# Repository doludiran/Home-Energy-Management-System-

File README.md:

# Home-Energy-Management-System-
This system retrieves dynamic electricity pricing information from a utility portal and automatically schedules  large residential loads like EV charging to reduce the overall cost of energy consumed 

The design involves and consists of:
• A Central Control Unit using a Linux based Raspberry Pi programmed in Python. Components of this unit included a touch screen graphic
user interface, secure Internet interface for the automatic retrieval of dynamic pricing information from a utility web portal and xbee wireless
communication interface (zigbee) for remote switching as well as load telemetry data transmission
• A Device Energy Monitoring Unit using an ARM Cortex-M3 based Microcontroller. Components of this unit included a xbee wireless interface
(zigbee) for transmitting monitoring data as well as receiving switching commands from the Central Control Unit, Analog Circuitry for AC load
switching and power consumption measurement (AC Voltage and Current)
• An optimization algorithm to minimize power cost using SciPY
• Multi-threaded programming in c and Python
• Printed Circuit Boards (PCB) design including soldering of Surface-Mount ICs (SMT)
• Hardware and printed circuit board testing and validation
• Component selection and assembly designed to comply with CSA standards

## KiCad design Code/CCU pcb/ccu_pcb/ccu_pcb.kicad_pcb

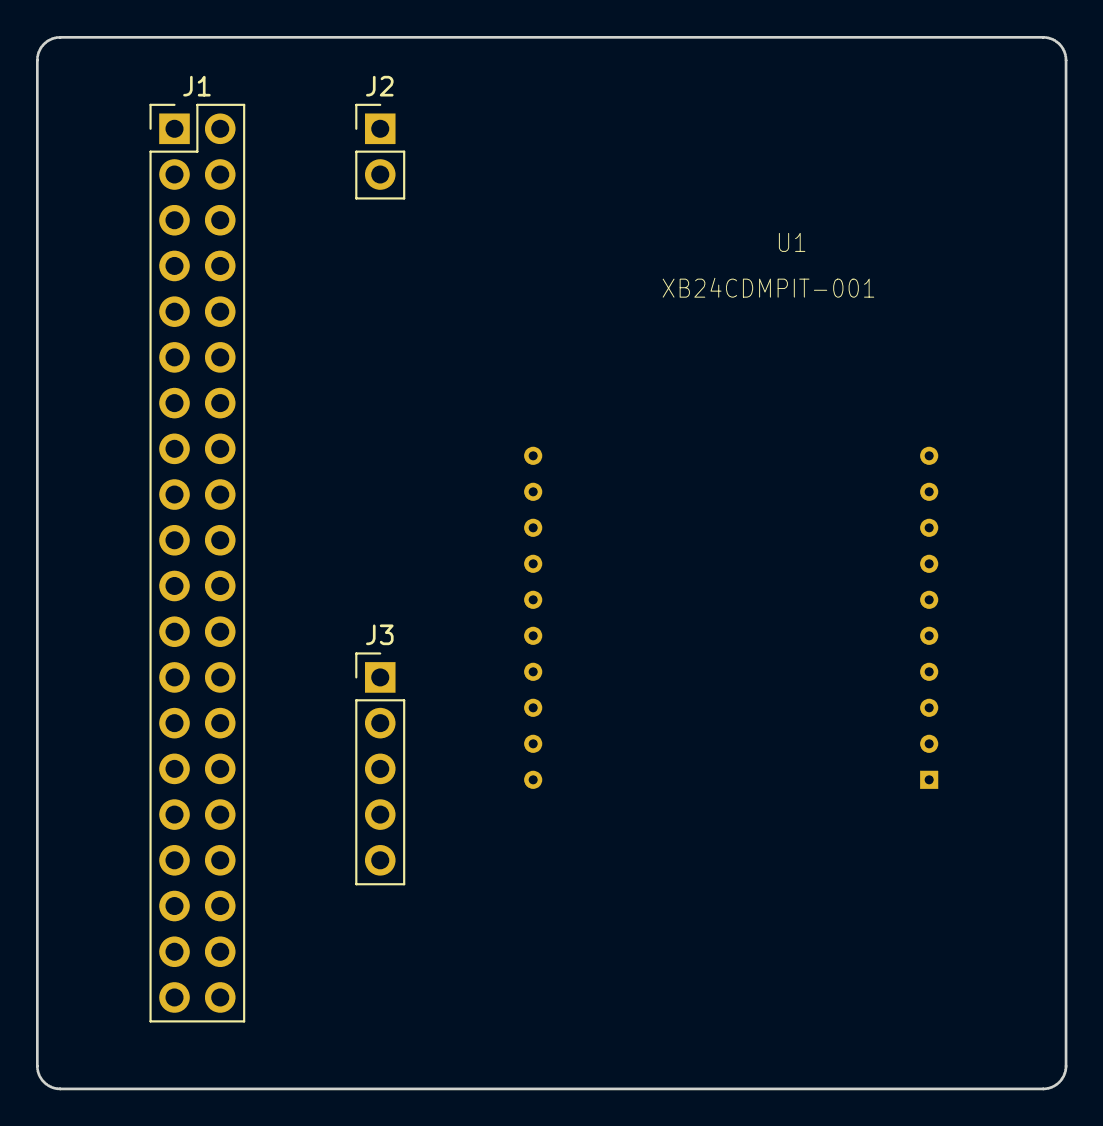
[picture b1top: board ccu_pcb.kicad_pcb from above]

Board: 2 copper layers, 57.2 x 58.4 mm, 4 parts (0 on the bottom side), 8 nets, no tracks yet.

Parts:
J1: Conn_02x20_Odd_Even; PinHeader_2x20_P2.54mm_Vertical
J2: Conn_01x02_Male; PinHeader_1x02_P2.54mm_Vertical
J3: Conn_01x05_Male; PinHeader_1x05_P2.54mm_Vertical
U1: XB24CDMPIT-001; DIP-20

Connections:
5Vsupply: J1.2, J2.1, J3.1
GND: J1.40, J2.2, J3.5, U1.10
Therm_in_c: J1.18, J3.4
Therm_in_h: J1.16, J3.3
Therm_out: J1.12, J3.2
VCC: J1.1, U1.1
X_DIN: J1.8, U1.3
X_DOUT: J1.10, U1.2

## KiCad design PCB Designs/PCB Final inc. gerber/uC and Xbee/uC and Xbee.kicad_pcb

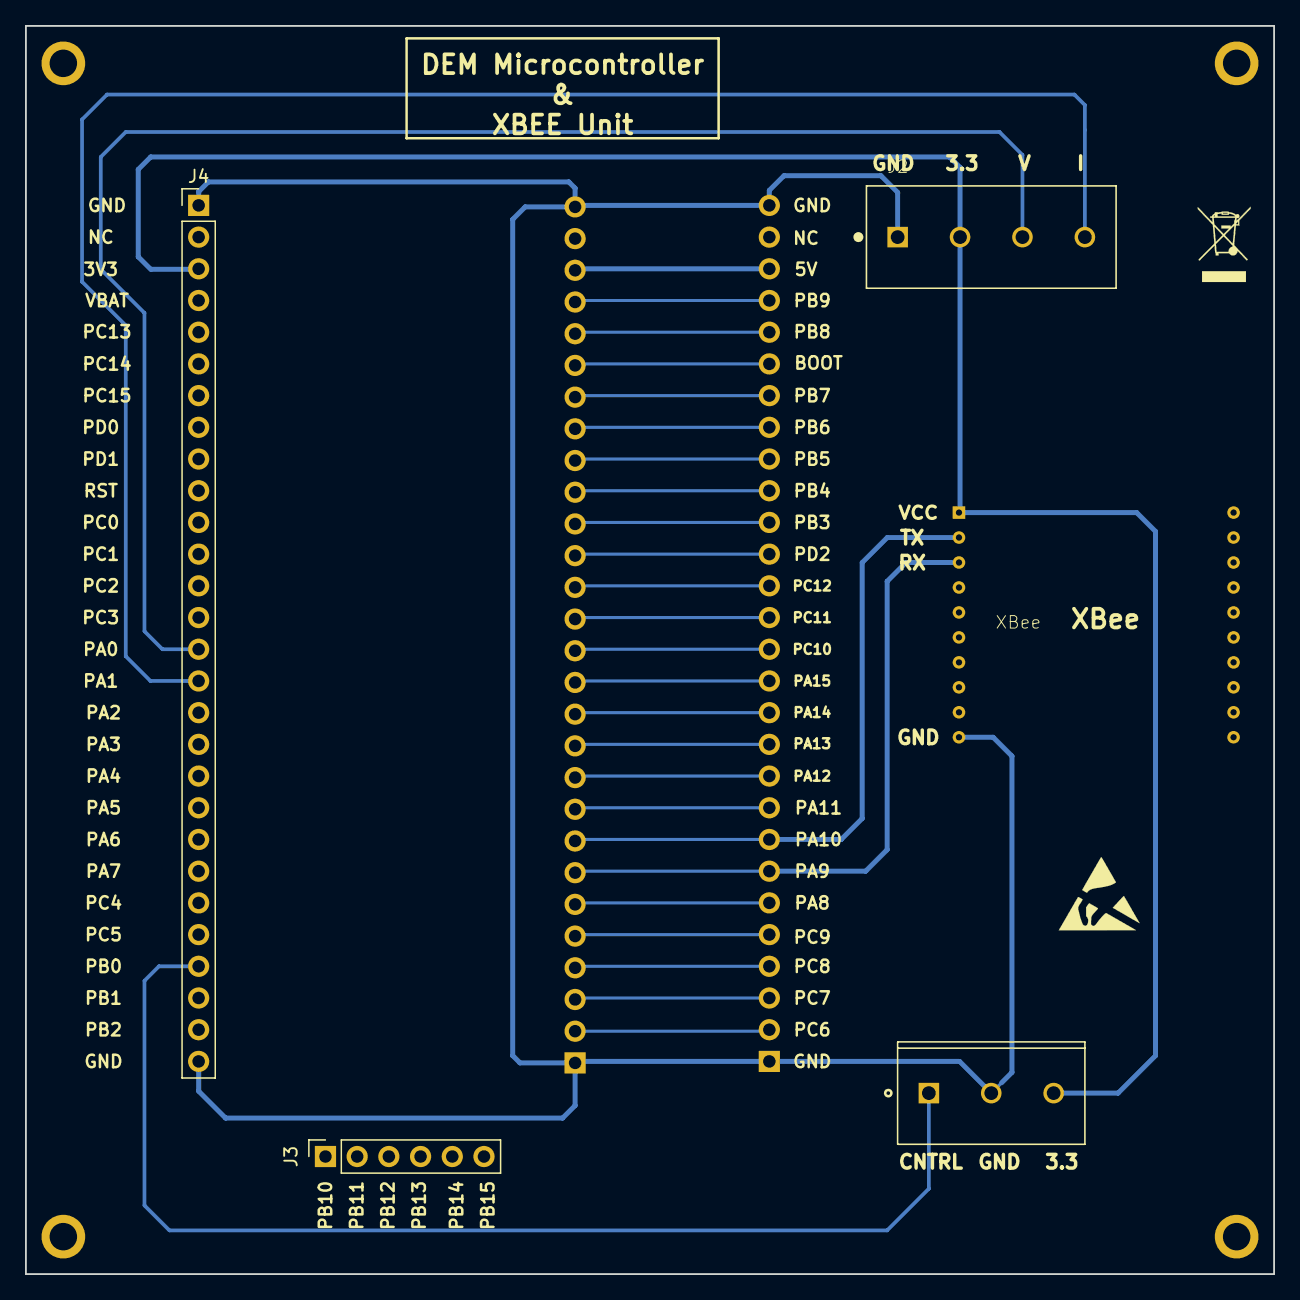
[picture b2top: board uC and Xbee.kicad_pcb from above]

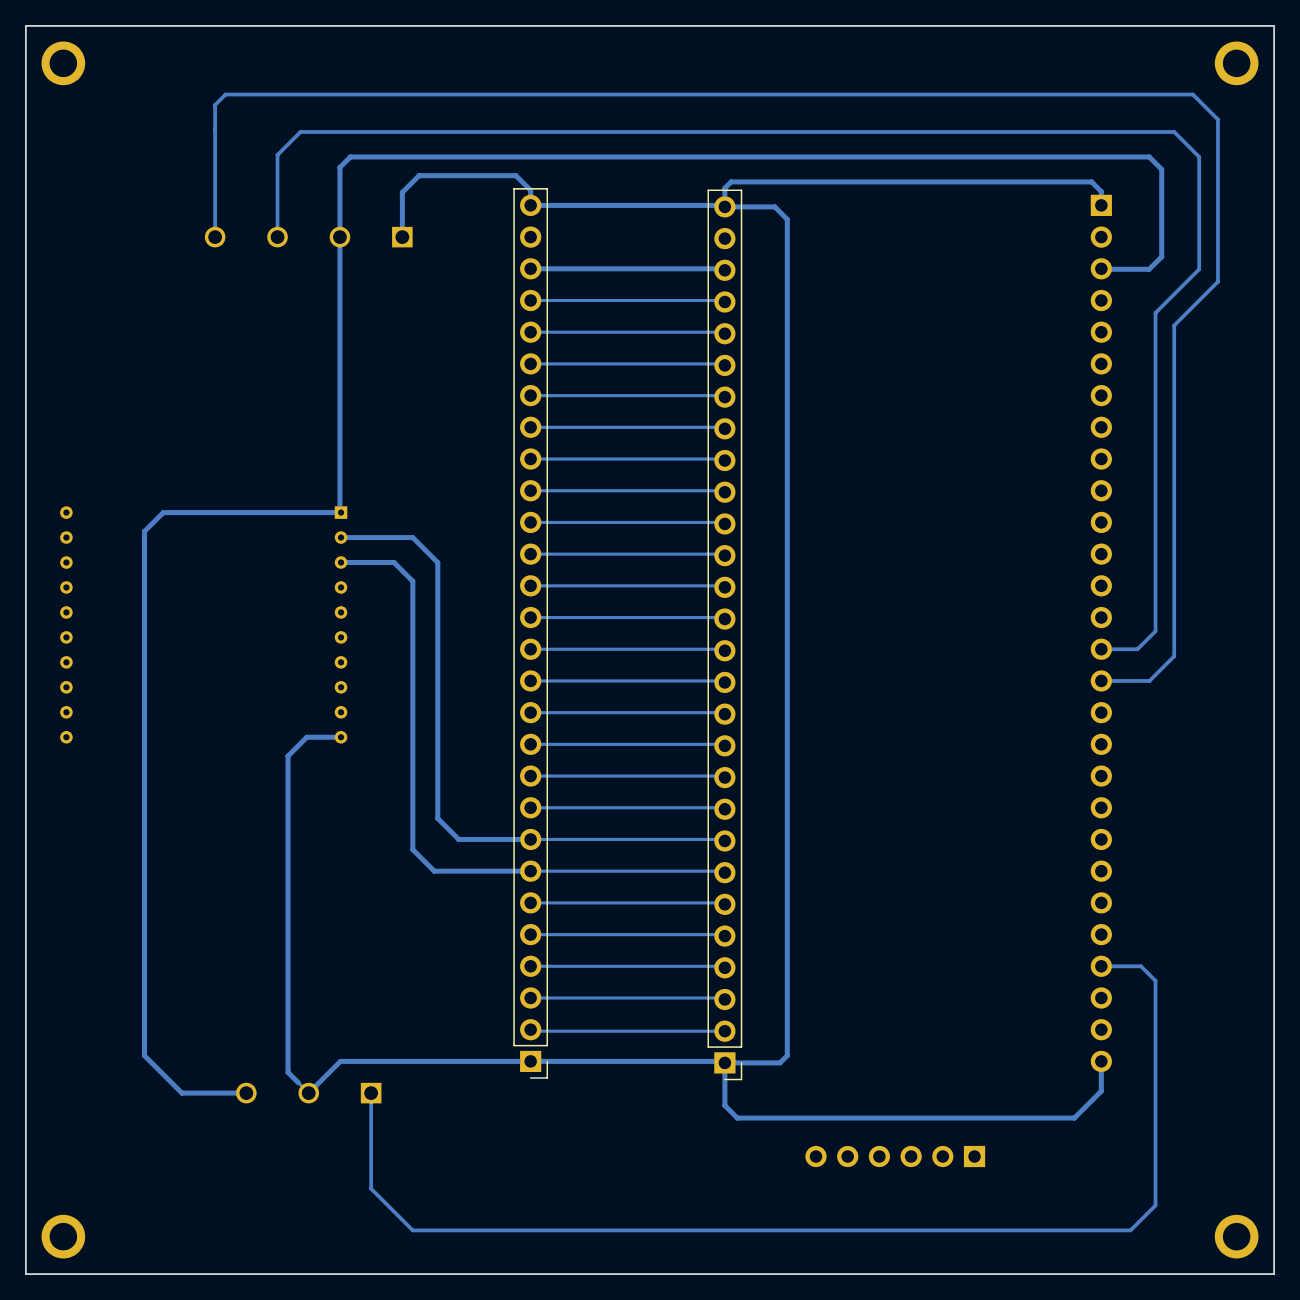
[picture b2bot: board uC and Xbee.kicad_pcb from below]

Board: 2 copper layers, 100.0 x 100.0 mm, 7 parts (2 on the bottom side), 30 nets.

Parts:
J1: 282836-3; TE_282836-3
J2: 282836-4; TE_282836-4
J3: Conn_01x06_Female; PinSocket_1x06_P2.54mm_Vertical
J4, J5, J6: Conn_01x28_Female; PinHeader_1x28_P2.54mm_Vertical
U1: XB24CDMSIT-001; DIP-20

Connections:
3.3V1: J1.3, J2.2, J4.3, U1.1
5V: J5.26, J6.26
BOOT: J5.23, J6.23
GND1: J1.2, J2.1, J4.1, J4.28, J5.1, J5.28, J6.1, J6.28, U1.10
PA0: J2.3, J4.15
PA1: J2.4, J4.16
PA8: J5.6, J6.6
PA9: J5.7, J6.7, U1.3
PA10: J5.8, J6.8, U1.2
PA11: J5.9, J6.9
PA12: J5.10, J6.10
PA13: J5.11, J6.11
PA14: J5.12, J6.12
PA15: J5.13, J6.13
PB0: J1.1, J4.25
PB3: J5.18, J6.18
PB4: J5.19, J6.19
PB5: J5.20, J6.20
PB6: J5.21, J6.21
PB7: J5.22, J6.22
PB8: J5.24, J6.24
PB9: J5.25, J6.25
PC6: J5.2, J6.2
PC7: J5.3, J6.3
PC8: J5.4, J6.4
PC9: J5.5, J6.5
PC10: J5.14, J6.14
PC11: J5.15, J6.15
PC12: J5.16, J6.16
PD2: J5.17, J6.17

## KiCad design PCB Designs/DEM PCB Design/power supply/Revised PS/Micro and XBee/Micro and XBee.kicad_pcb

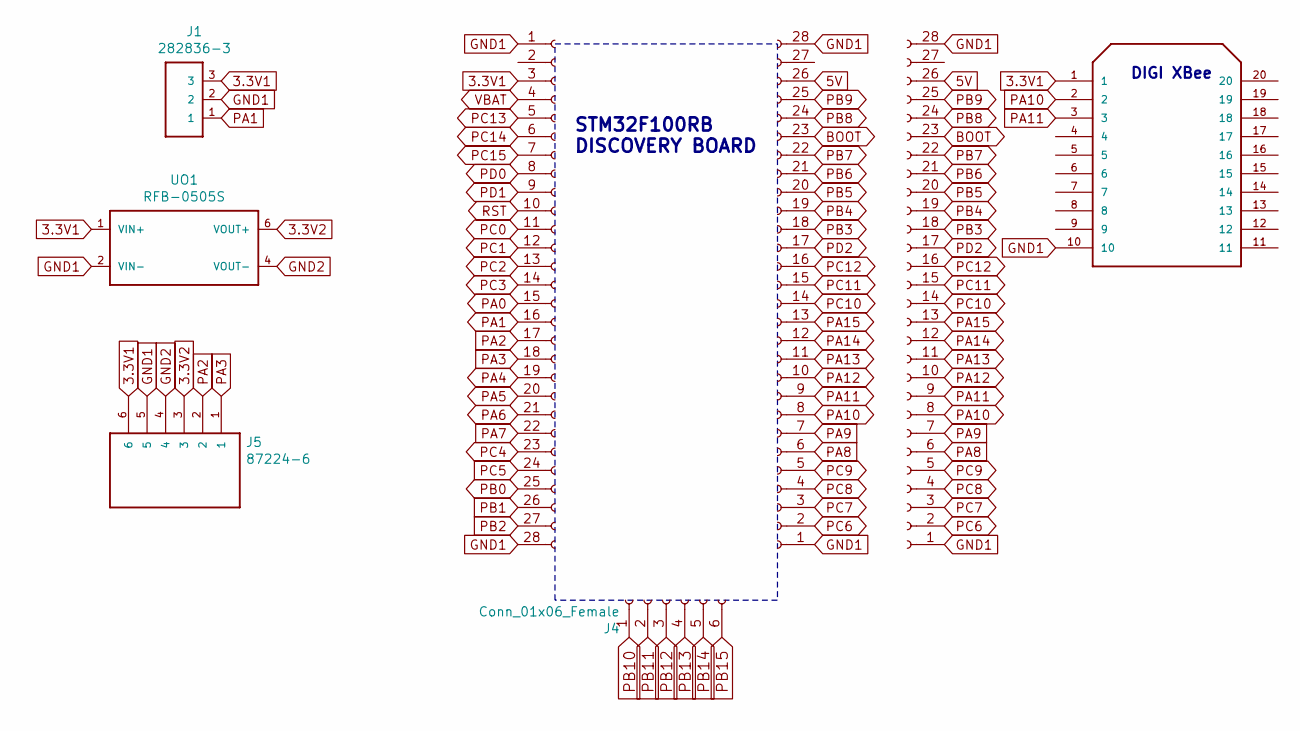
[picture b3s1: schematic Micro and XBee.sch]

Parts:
J1: 282836-3; TE_282836-3
J2, J3, J6: Conn_01x28_Female; PinHeader_1x28_P2.54mm_Vertical
J4: Conn_01x06_Female; PinSocket_1x06_P2.54mm_Vertical
J5: 87224-6; TE_87224-6
U2: XB24CDMSIT-001; DIP-20
UO1: RFB-0505S

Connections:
3.3V1: J1.3, J2.3, J5.6, U2.1, UO1.1 (VIN+)
3.3V2: J5.3, UO1.6 (VOUT+)
5V: J3.26, J6.26
BOOT: J3.23, J6.23
GND1: J1.2, J2.1, J2.28, J3.1, J3.28, J5.5, J6.1, J6.28, U2.10, UO1.2 (VIN-)
GND2: J5.4, UO1.4 (VOUT-)
PA0: J2.15
PA1: J1.1, J2.16
PA2: J2.17, J5.2
PA3: J2.18, J5.1
PA4: J2.19
PA5: J2.20
PA6: J2.21
PA7: J2.22
PA8: J3.6, J6.6
PA9: J3.7, J6.7
PA10: J3.8, J6.8, U2.2
PA11: J3.9, J6.9, U2.3
PA12: J3.10, J6.10
PA13: J3.11, J6.11
PA14: J3.12, J6.12
PA15: J3.13, J6.13
PB0: J2.25
PB1: J2.26
PB2: J2.27
PB3: J3.18, J6.18
PB4: J3.19, J6.19
PB5: J3.20, J6.20
PB6: J3.21, J6.21
PB7: J3.22, J6.22
PB8: J3.24, J6.24
PB9: J3.25, J6.25
PB10: J4.1
PB11: J4.2
PB12: J4.3
PB13: J4.4
PB14: J4.5
PB15: J4.6
PC0: J2.11
PC1: J2.12
PC2: J2.13
PC3: J2.14
PC4: J2.23
PC5: J2.24
PC6: J3.2, J6.2
PC7: J3.3, J6.3
PC8: J3.4, J6.4
PC9: J3.5, J6.5
PC10: J3.14, J6.14
PC11: J3.15, J6.15
PC12: J3.16, J6.16
PC13: J2.5
PC14: J2.6
PC15: J2.7
PD0: J2.8
PD1: J2.9
PD2: J3.17, J6.17
RST: J2.10
VBAT: J2.4

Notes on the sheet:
STM32F100RB DISCOVERY BOARD
DIGI XBee

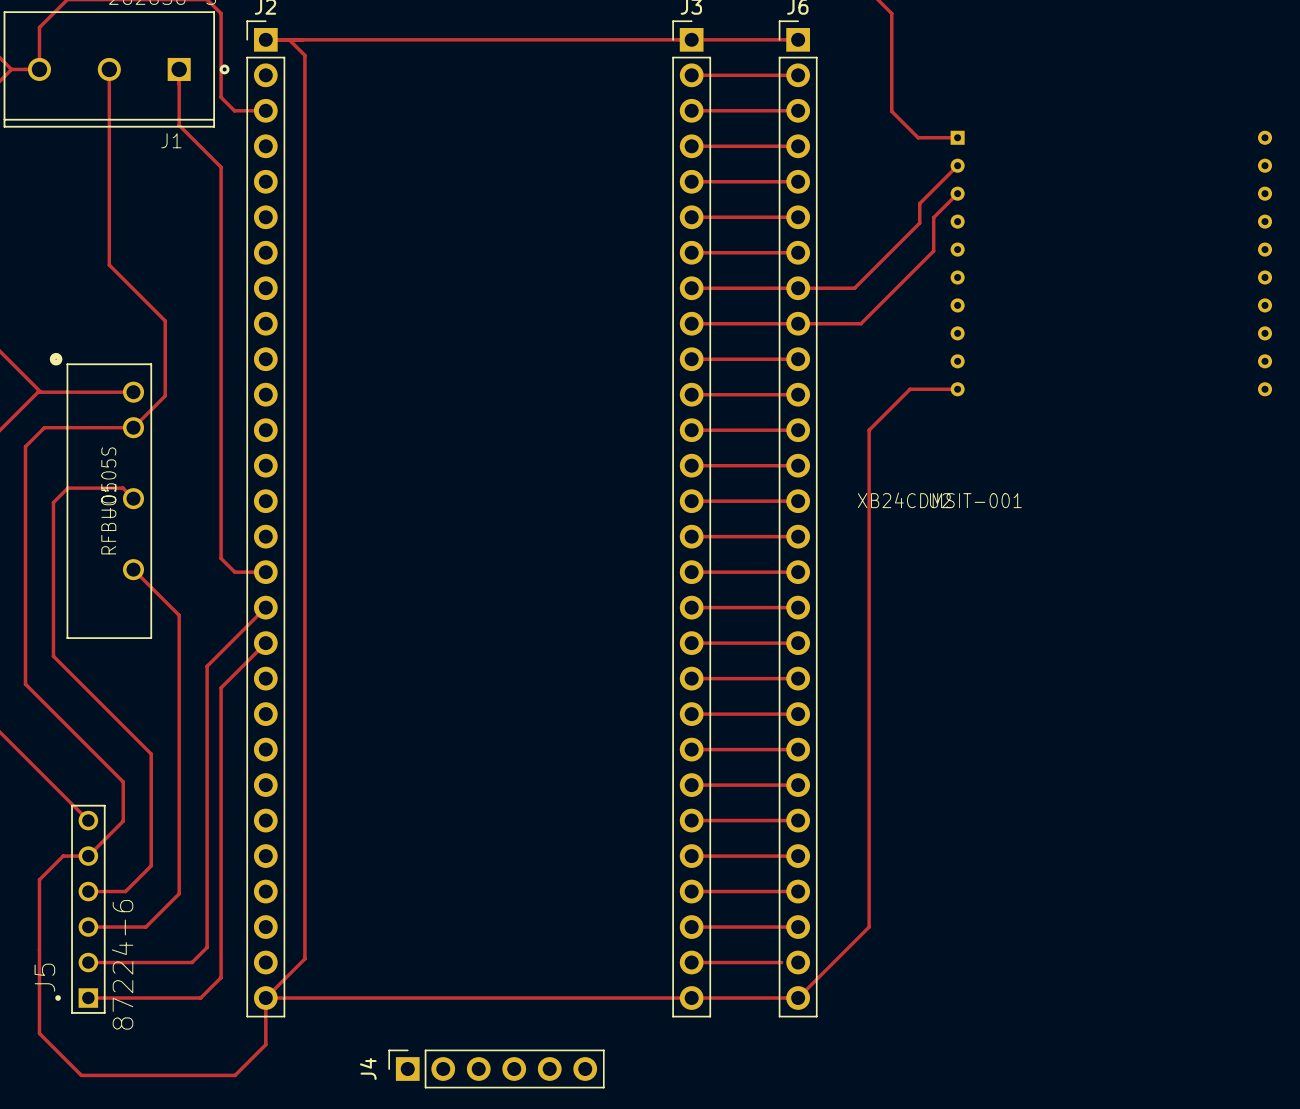
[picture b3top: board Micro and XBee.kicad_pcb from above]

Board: 2 copper layers, 8 parts (0 on the bottom side), 32 nets.

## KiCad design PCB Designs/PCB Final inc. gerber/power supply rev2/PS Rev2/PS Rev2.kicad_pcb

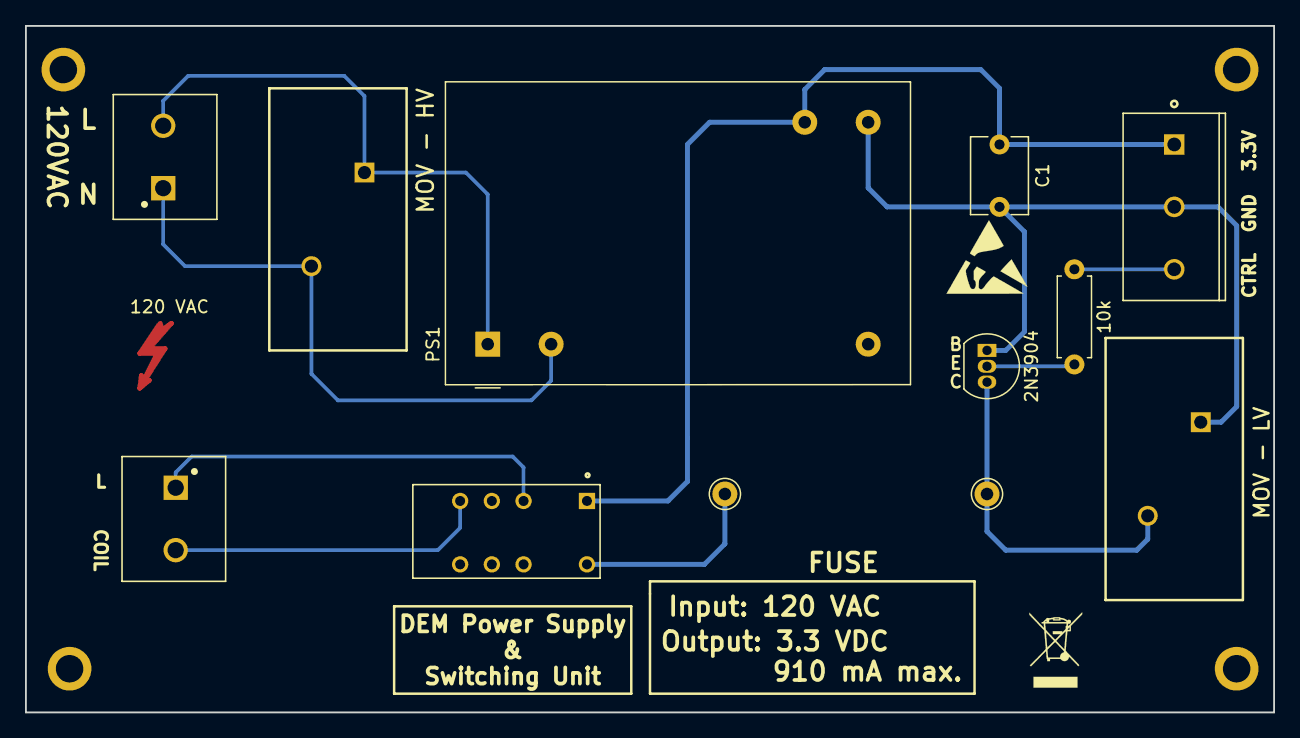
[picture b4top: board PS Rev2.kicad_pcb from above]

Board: 2 copper layers, 100.0 x 55.0 mm, 13 parts (0 on the bottom side), 10 nets.

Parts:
2N3904: 2N3904; TO-92_Inline
10k: 10k; R_Axial_DIN0207_L6.3mm_D2.5mm_P7.62mm_Horizontal
120 VAC : Symbol_Highvoltage_Type1_CopperTop_Small
C1: 400 nF; C_Disc_D6.0mm_W4.4mm_P5.00mm
J1, J3: 1935161; PHOENIX_1935161
J2: 282836-3; TE_282836-3
J4, J5: Conn_01x01_Female; Pin_D1.0mm_L10.0mm
K1: EC2-3NU; KEMET_EC2-3NU
MOV - HV: TMOV20RP300E; CAPRR750W81L2100T1100H2300P
MOV - LV: TMOV20RP300E; CAPRR750W81L2100T1100H2300P
PS1: RAC03-3.3SGA; Converter_ACDC_RECOM_RAC04-xxSGx_THT

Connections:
unnamed: C1.1, J2.1, K1.1, PS1.5
unnamed: 2N3904.1, C1.2, J2.2, MOV - LV.1, PS1.4
unnamed: J1.1, MOV - HV.2, PS1.2
unnamed: J1.2, MOV - HV.1, PS1.1
unnamed: 10k.1, J2.3
unnamed: J3.1, K1.3
unnamed: J3.2, K1.5
unnamed: 2N3904.3, J4.1, MOV - LV.2
unnamed: J5.1, K1.12
unnamed: 2N3904.2, 10k.2

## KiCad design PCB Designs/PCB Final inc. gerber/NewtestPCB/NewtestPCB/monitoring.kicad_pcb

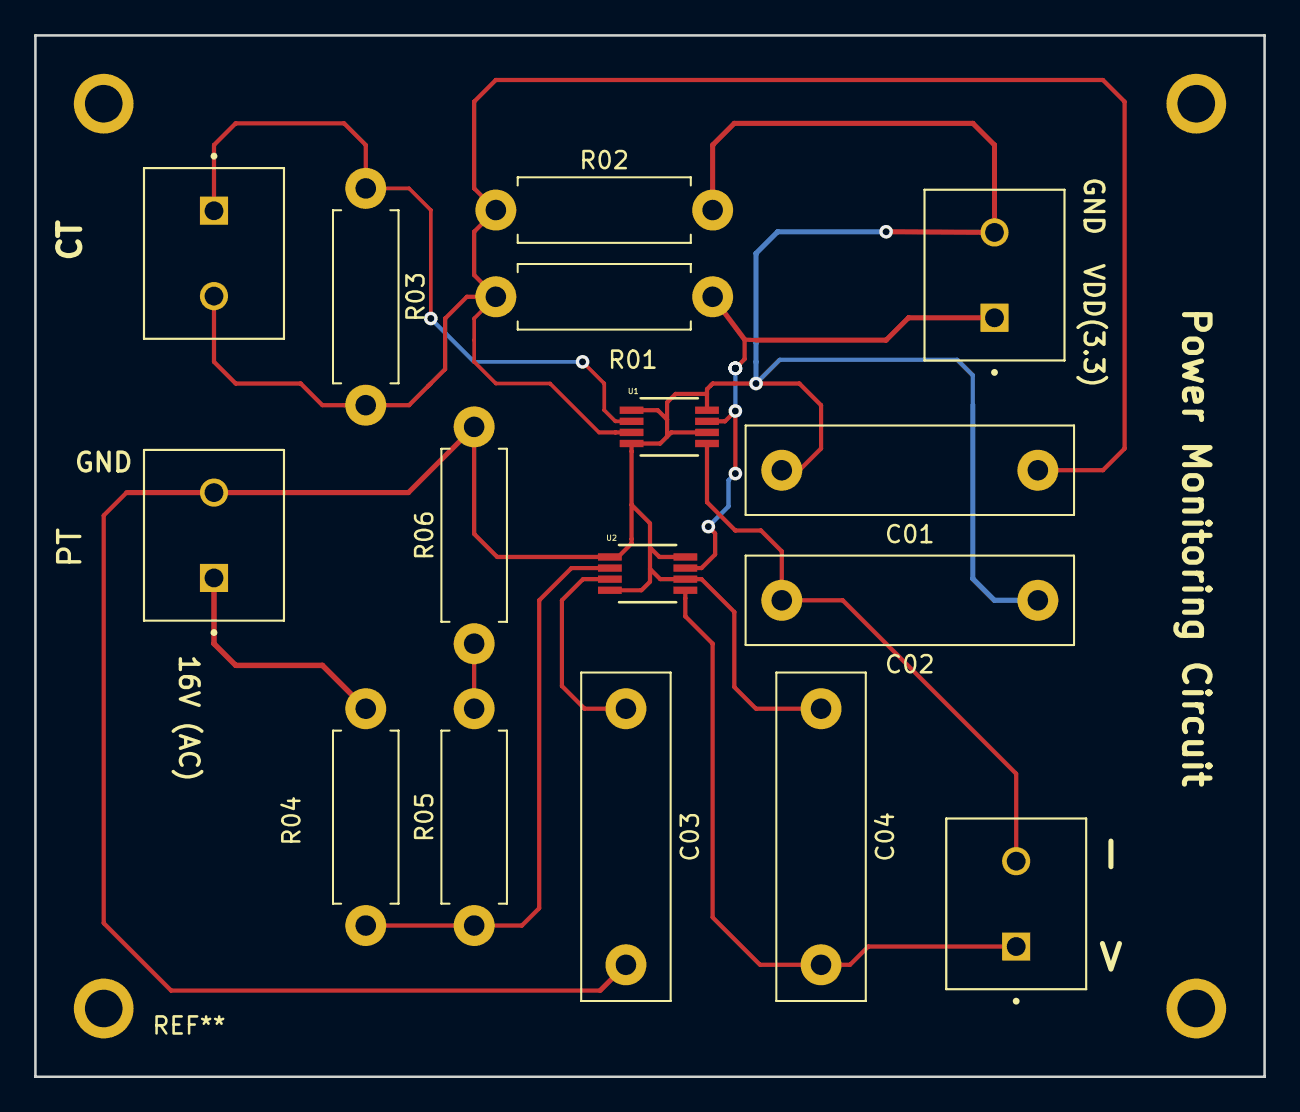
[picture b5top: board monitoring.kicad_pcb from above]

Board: 2 copper layers, 72.0 x 61.0 mm, 16 parts (0 on the bottom side), 10 nets.

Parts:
C01, C03: 0.1uF; C_Rect_L19.0mm_W5.0mm_P15.00mm_MKS4
C02, C04: 1uF; C_Rect_L19.0mm_W5.0mm_P15.00mm_MKS4
CT: 282836-2; CONN_282836-2
J3, J4: 282836-2; CONN_282836-2
PT: 282836-2; CONN_282836-2
R01, R02: 100k; R_Axial_DIN0411_L9.9mm_D3.6mm_P12.70mm_Horizontal
R03: 4; R_Axial_DIN0411_L9.9mm_D3.6mm_P12.70mm_Horizontal
R04: 10k; R_Axial_DIN0411_L9.9mm_D3.6mm_P12.70mm_Horizontal
R05: 215k; R_Axial_DIN0411_L9.9mm_D3.6mm_P12.70mm_Horizontal
R06: 1k; R_Axial_DIN0411_L9.9mm_D3.6mm_P12.70mm_Horizontal
U1, U2: LTC1966CMS8PBF; MSOP-8_MS

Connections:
unnamed: C01.1, CT.2, R01.2, R02.1, R03.2, U1.3
unnamed: C01.2, C02.1, C03.2, C04.1, J3.2, PT.2, R02.2, R06.2, U1.1, U1.4, U1.6, U1.8, U2.1, U2.4, U2.6, U2.8
unnamed: C02.2, J4.2, U1.5
unnamed: C03.1, U2.3
unnamed: C04.2, J4.1, U2.5
unnamed: CT.1, R03.1, U1.2
unnamed: PT.1, R04.1
unnamed: J3.1, R01.1, U1.7, U2.7
unnamed: R04.2, R05.1, U2.2
unnamed: R05.2, R06.1

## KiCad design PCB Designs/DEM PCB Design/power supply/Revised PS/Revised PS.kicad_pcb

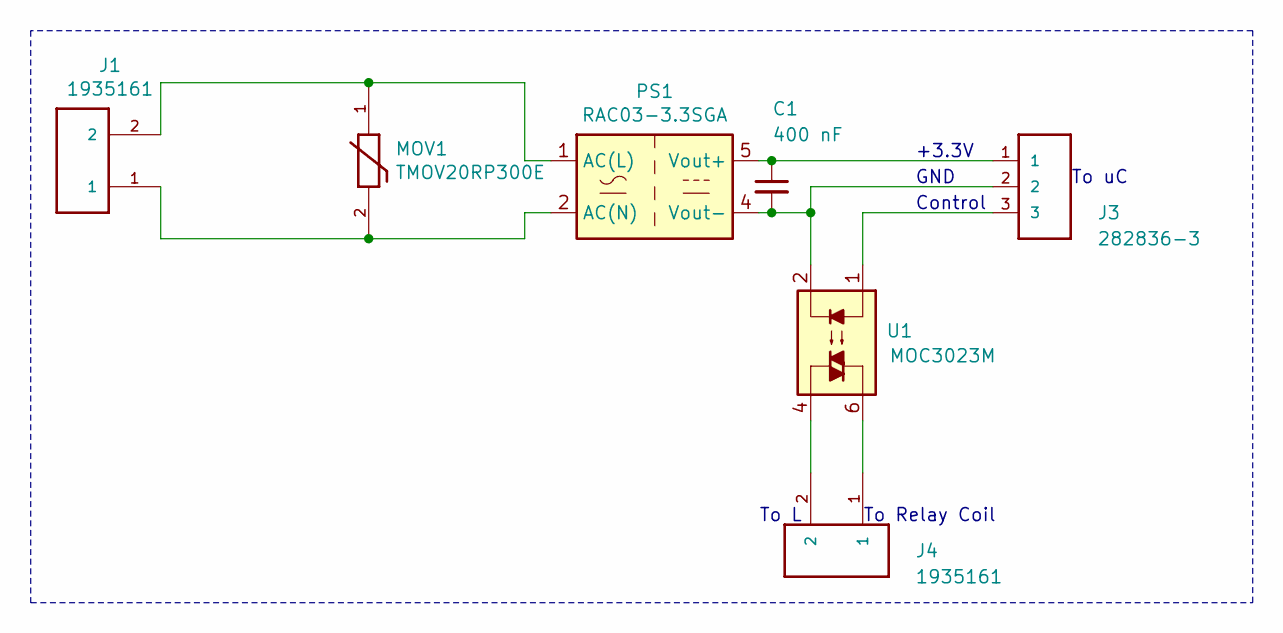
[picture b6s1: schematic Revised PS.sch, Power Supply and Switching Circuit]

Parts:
C1: 400 nF; C_Disc_D6.0mm_W4.4mm_P5.00mm
J1, J4: 1935161; PHOENIX_1935161
J3: 282836-3; TE_282836-3
MOV1: TMOV20RP300E; CAPRR750W81L2100T1100H2300P
PS1: RAC03-3.3SGA; Converter_ACDC_RECOM_RAC04-xxSGx_THT
U1: MOC3023M; DIP762W48P254L889H508Q6

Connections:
unnamed: C1.1, J3.1, PS1.5 (Vout+)
unnamed: C1.2, J3.2, PS1.4 (Vout-), U1.2
unnamed: J1.1, MOV1.2, PS1.2 (AC(N))
unnamed: J1.2, MOV1.1, PS1.1 (AC(L))
unnamed: J3.3, U1.1
unnamed: J4.1, U1.6
unnamed: J4.2, U1.4

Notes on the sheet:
To Relay Coil
To L
+3.3V
GND
Control
To uC

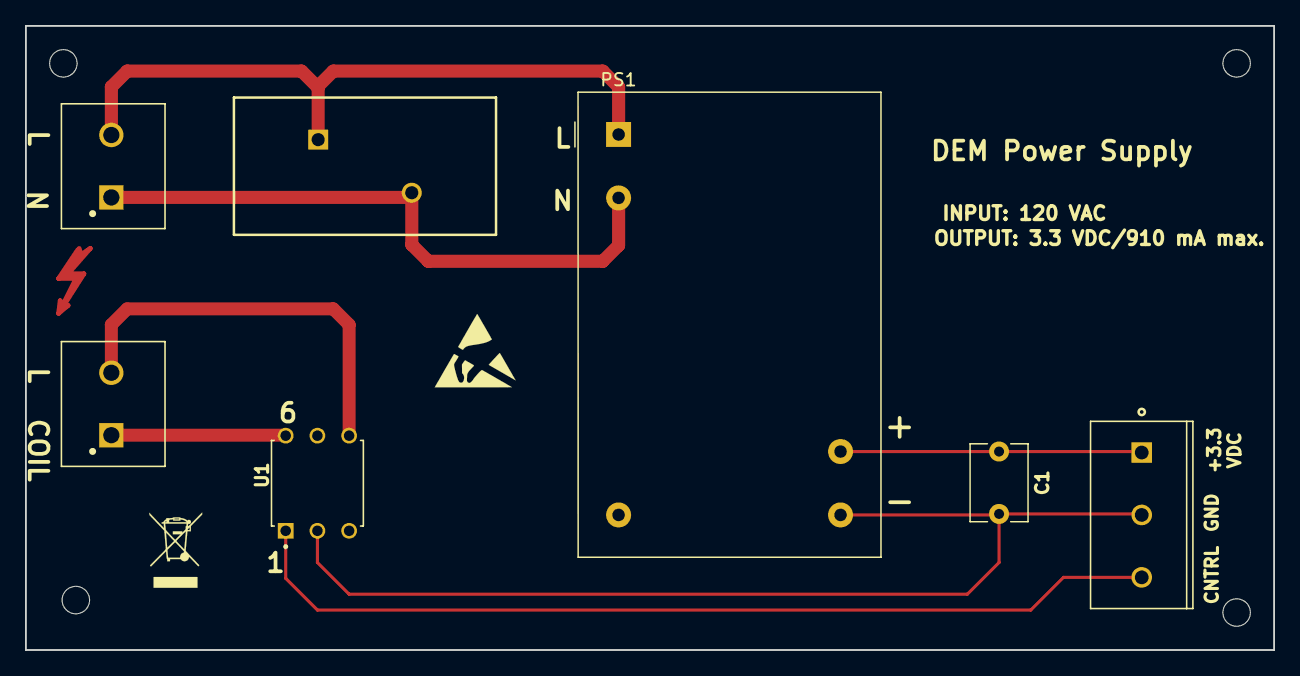
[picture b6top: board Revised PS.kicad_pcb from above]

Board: 2 copper layers, 100.0 x 50.0 mm, 7 parts (0 on the bottom side), 7 nets.

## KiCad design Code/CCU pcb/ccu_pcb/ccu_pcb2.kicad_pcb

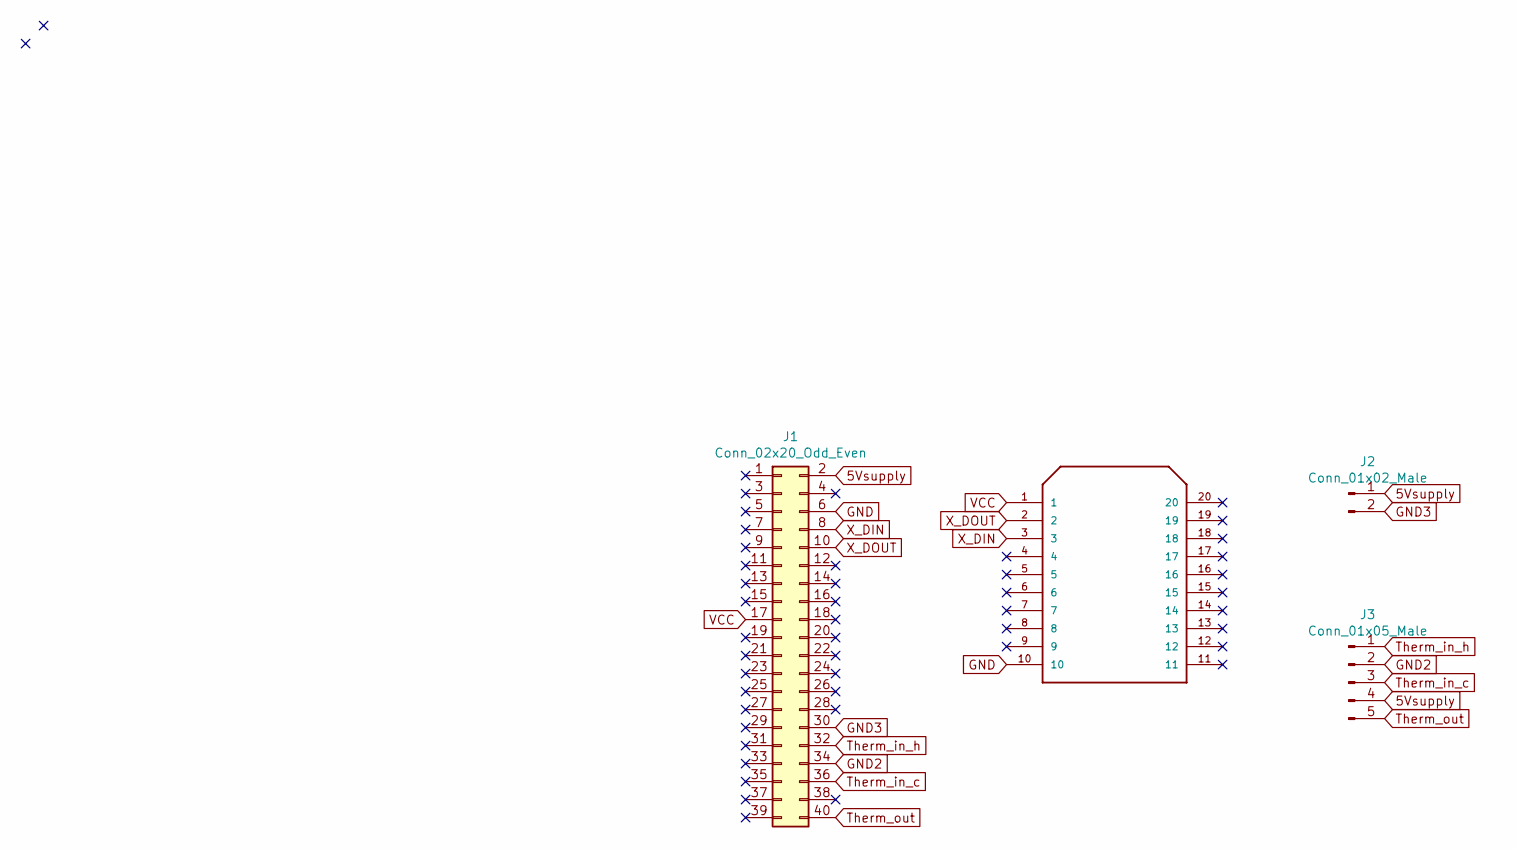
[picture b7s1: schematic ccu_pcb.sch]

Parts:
J1: Conn_02x20_Odd_Even; PinHeader_2x20_P2.54mm_Vertical
J2: Conn_01x02_Male; PinHeader_1x02_P2.54mm_Vertical
J3: Conn_01x05_Male; PinHeader_1x05_P2.54mm_Vertical
U1: XB24CDMPIT-001; DIP-20

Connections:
5Vsupply: J1.2, J2.1, J3.4
GND: J1.6, U1.10
GND2: J1.34, J3.2
GND3: J1.30, J2.2
Therm_in_c: J1.36, J3.3
Therm_in_h: J1.32, J3.1
Therm_out: J1.40, J3.5
VCC: J1.17, U1.1
X_DIN: J1.8, U1.3
X_DOUT: J1.10, U1.2

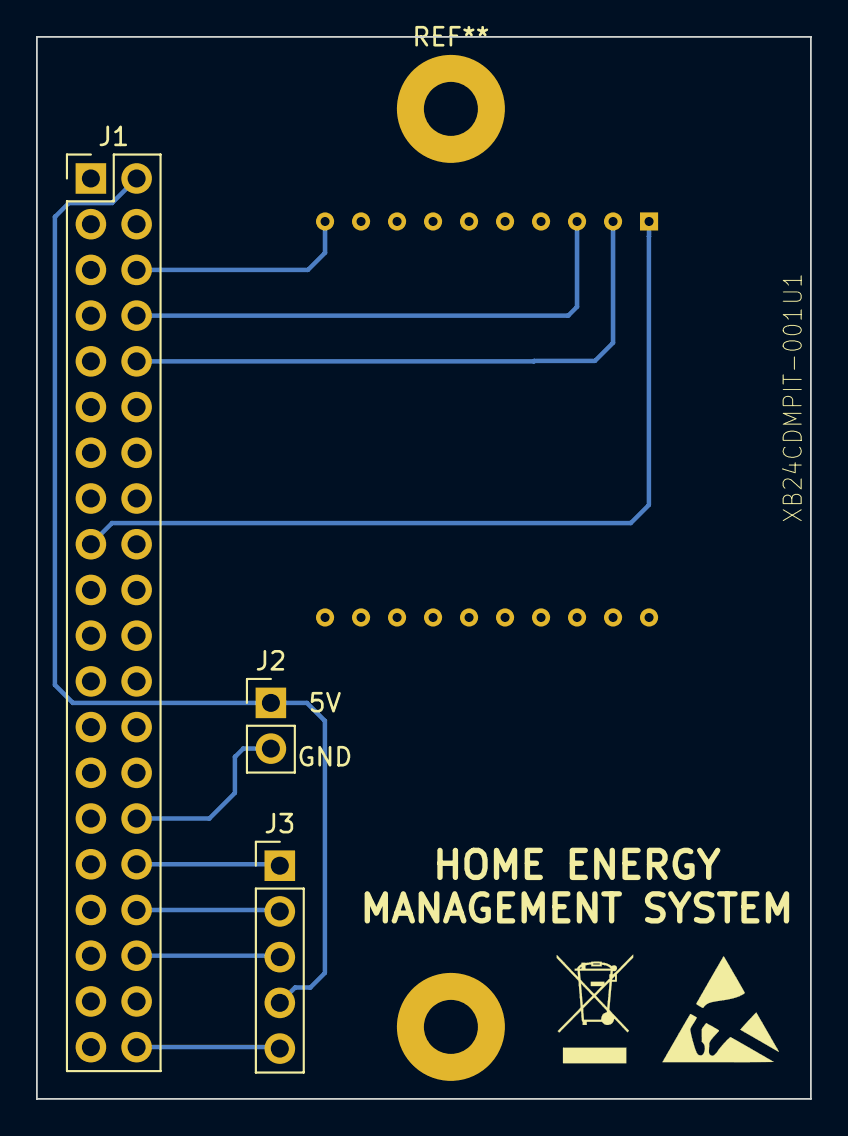
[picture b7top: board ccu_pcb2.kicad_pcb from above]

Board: 2 copper layers, 43.0 x 59.0 mm, 4 parts (0 on the bottom side), 10 nets.

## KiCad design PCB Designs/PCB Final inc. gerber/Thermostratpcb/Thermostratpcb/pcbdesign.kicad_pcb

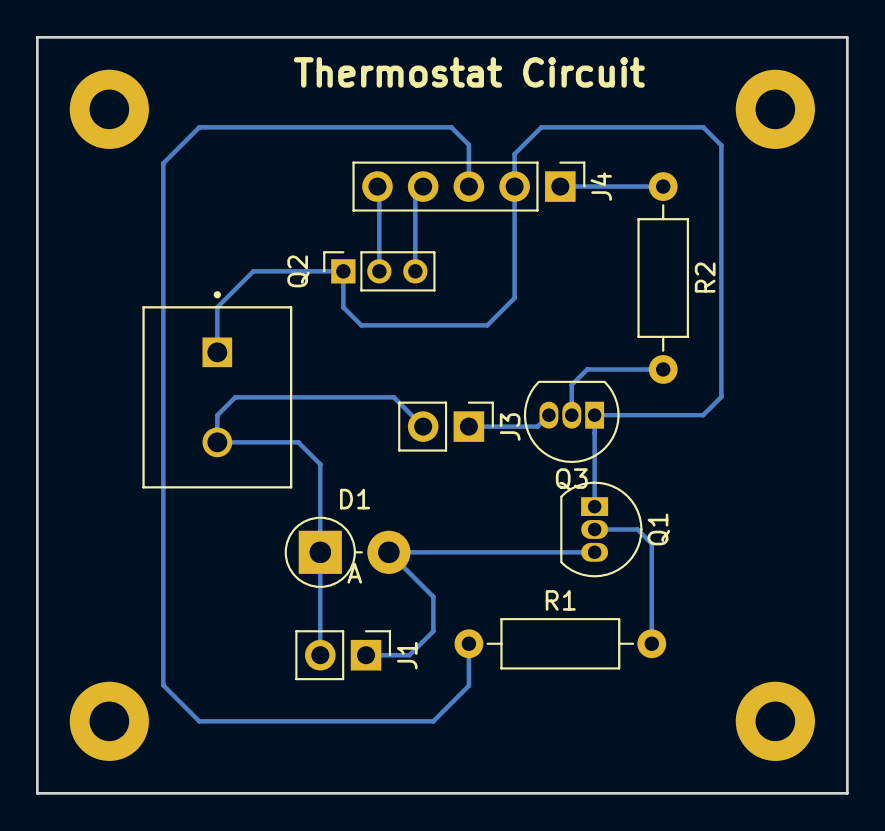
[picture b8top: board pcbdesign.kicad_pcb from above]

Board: 2 copper layers, 45.0 x 42.0 mm, 10 parts (0 on the bottom side), 10 nets.

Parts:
D1: 1N4001; D_DO-15_P3.81mm_Vertical_AnodeUp
J1, J3: Conn_01x02_Male; PinHeader_1x02_P2.54mm_Vertical
J2: 282836-2; CONN_282836-2
J4: Conn_01x05_Male; PinHeader_1x05_P2.54mm_Vertical
Q1, Q3: 2N3904; TO-92_Inline
Q2: DS18B20+PAR; PinSocket_1x03_P2.00mm_Vertical
R1, R2: R; R_Axial_DIN0207_L6.3mm_D2.5mm_P10.16mm_Horizontal

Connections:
unnamed: D1.1, J1.2, J2.2, J3.2
unnamed: D1.2, J1.1, Q1.3
unnamed: J2.1, J4.2, Q1.1, Q2.1, Q3.1
unnamed: J3.1, Q3.3
unnamed: J4.1, R2.1
unnamed: J4.3, R1.1
unnamed: J4.4, Q2.3
unnamed: J4.5, Q2.2
unnamed: Q1.2, R1.2
unnamed: Q3.2, R2.2

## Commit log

2018-12-03 Project design presentation
2018-12-03 Soc datasheet
2019-01-16 Initial Commit
    Capstone User Interface design:
    - Created initial layout for all screens
    - Added transitions an some button functionality
    - Retrieved Data from local myslite3 database
    - Graphical representation for Time of Use Data
2019-01-16 Initial drafts of the commissioning documents for the CCUGUI design and Zigbee Communications
2019-01-16 Parts Documentation and Resources
2019-01-16 Project Tracker
    For Scheduling and Progress Tracking as well as Task Assignment
2019-01-16 - Restructured kivy code - Changed ToU Data presentation
2019-01-17 Word document template for all the testing plans
2019-01-17 Research for the capstone project
2019-01-17 Reorganization of folders
2019-01-17 Modified subsystem test plans
2019-01-17 CT and temperature sensor datasheet
2019-01-17 Utility portal Frontend Code
2019-01-18 Commissiong document CT,Thermostat and portal
2019-01-22 Refactoring code for deployment on Raspberry Pi
2019-01-25 Python script to remotely access MySQL using port forwadring and mysql client.
2019-02-23 CCU Enclosure design
    - made box part
2019-02-23 Xbee Communication for CCU
    - Created xbee class with preliminary send and receive methods
2019-02-23 DEM Communication Interface
    Serial Interface:
    - initialization
    - Serial transmit
    - USART ISR for serial receive
    Xbee Interface
    - Send function to send over serial interface
2019-02-23 Linear Optimization Algorithms for DR implementation
2019-02-23 DR Optimization Resource for Dr Wang
2019-02-23 Changed App layout and formatting for pi deployment
2019-02-25 added a user input screen for scheduling
2019-03-02 Xbee comms for CCU. send and receive methods.
2019-03-02 DEM comms tested and verified
2019-03-02 Testing plan updates. -comms link tested and verified
2019-03-02 no message
2019-03-07 Utility Data retrieval and data formatting
2019-03-09 Revert "no message"
    This reverts commit 587cd837fc0db71fd895eb2b1a76b997976c0c9b.
2019-03-09 Trying to fix pull error. Test 1
2019-03-09 Remove space in folder name
2019-03-10 pull error check - resolving pull issue
2019-03-11 Added Zigbee range testing documentation
2019-03-12 1. The power supply and switching circuit testing results 2. Results of end to end switching Note: Delayed push due to pull errors on sourcetree
2019-03-12 Power monitoring code: Only switching circuit tested end to end - working Derived equations from the data measured from RMS to DC convertor: Power Monitoring Curve Fiting
2019-03-14 Could not update earlier due to pull error. Power supply and switching circuit PCB desgins - Rev1 and Rev2 (final) Microcontroller and Xbee PCB Design - (Rev1 and Rev2(final) Also, final PCB designs 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
2019-03-17 Recent changes to GUI and App functions and appearances(Post Crash)
2019-03-17 Final CCU PCB design
2019-03-17 New Threaded Xbee communications interface for CCU App
2019-03-18 Thread ToU json file retrieve module
2019-03-25 delayed due to pullerror
2019-03-27 Powermonitoring integration with switching
2019-03-29 Some test code is deleted for final version
2019-03-30 CCU integrated system
2019-04-08 Final Code clean up and documentation for DEM
2019-04-09 Final System Code (CCU)
2019-04-09 Final Testing Plan Results
